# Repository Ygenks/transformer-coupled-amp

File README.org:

* Размер трансформатора ДхШ: 52.5х40

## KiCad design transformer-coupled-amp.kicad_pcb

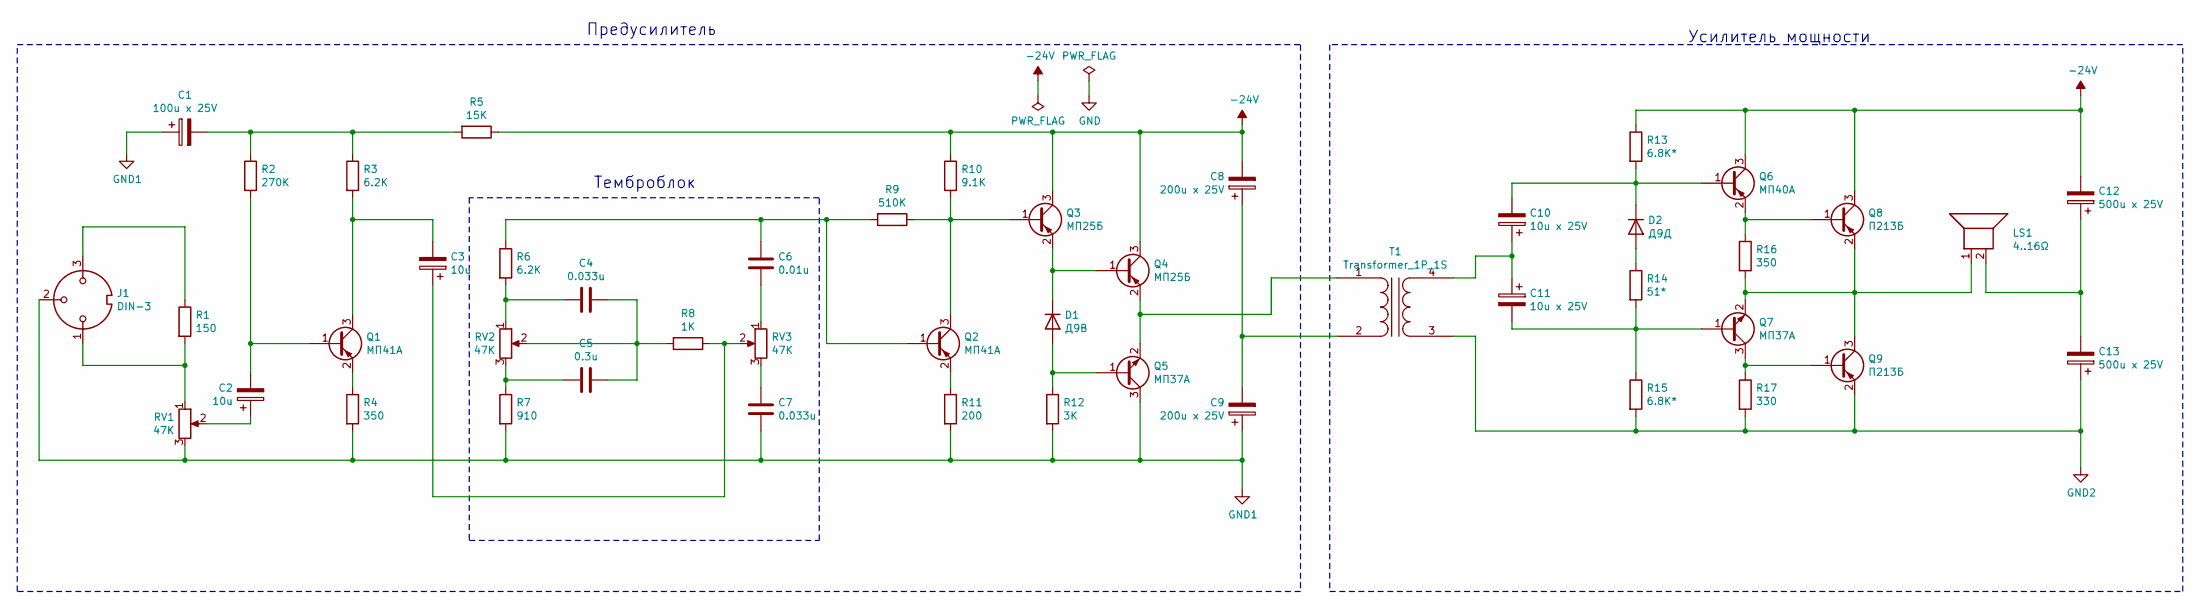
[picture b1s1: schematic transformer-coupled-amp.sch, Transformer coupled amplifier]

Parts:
C1: 100u x 25V; CP_Radial_D6.3mm_P2.50mm
C2, C3: 10u; CP_Radial_D5.0mm_P2.00mm
C4, C7: 0.033u; C_Disc_D10.0mm_W2.5mm_P5.00mm
C5: 0.3u; C_Rect_L18.0mm_W8.0mm_P15.00mm_FKS3_FKP3
C6: 0.01u; C_Rect_L13.0mm_W5.0mm_P10.00mm_FKS3_FKP3_MKS4
C8, C9: 200u x 25V; CP_Radial_D8.0mm_P3.50mm
C10, C11: 10u x 25V; CP_Radial_D5.0mm_P2.00mm
C12, C13: 500u x 25V; CP_Radial_D10.0mm_P5.00mm
D1: Д9В; D_DO-15_P15.24mm_Horizontal
D2: Д9Д; D_DO-15_P15.24mm_Horizontal
J1: DIN-3; PinHeader_1x03_P2.54mm_Vertical
LS1: 4..16Ω; PinHeader_1x02_P2.54mm_Vertical
Q1, Q2: МП41А; TO-5-3
Q3, Q4: МП25Б; TO-5-3
Q5, Q7: МП37А; TO-5-3
Q6: МП40A; TO-5-3
Q8, Q9: П213Б; PinHeader_1x03_P2.54mm_Vertical
R1: 150; R_Axial_DIN0207_L6.3mm_D2.5mm_P10.16mm_Horizontal
R2: 270K; R_Axial_DIN0207_L6.3mm_D2.5mm_P10.16mm_Horizontal
R3, R6: 6.2K; R_Axial_DIN0207_L6.3mm_D2.5mm_P10.16mm_Horizontal
R4: 350; R_Axial_DIN0207_L6.3mm_D2.5mm_P10.16mm_Horizontal
R5: 15K; R_Axial_DIN0207_L6.3mm_D2.5mm_P10.16mm_Horizontal
R7: 910; R_Axial_DIN0207_L6.3mm_D2.5mm_P10.16mm_Horizontal
R8: 1K; R_Axial_DIN0207_L6.3mm_D2.5mm_P10.16mm_Horizontal
R9: 510K; R_Axial_DIN0207_L6.3mm_D2.5mm_P10.16mm_Horizontal
R10: 9.1K; R_Axial_DIN0207_L6.3mm_D2.5mm_P10.16mm_Horizontal
R11: 200; R_Axial_DIN0207_L6.3mm_D2.5mm_P10.16mm_Horizontal
R12: 3K; R_Axial_DIN0207_L6.3mm_D2.5mm_P10.16mm_Horizontal
R13, R15: 6.8K*; R_Axial_DIN0309_L9.0mm_D3.2mm_P15.24mm_Horizontal
R14: 51*; R_Axial_DIN0309_L9.0mm_D3.2mm_P15.24mm_Horizontal
R16: 350; R_Axial_DIN0309_L9.0mm_D3.2mm_P15.24mm_Horizontal
R17: 330; R_Axial_DIN0309_L9.0mm_D3.2mm_P15.24mm_Horizontal
RV1, RV2, RV3: 47K; Potentiometer_Bourns_3386C_Horizontal
T1: Transformer_1P_1S; Transformer_44x40

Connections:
-24V: C8.2, C12.2, Q3.3 (C), Q4.3 (C), Q6.3 (C), Q8.3 (C), R5.1, R10.1, R13.1
GND1: C1.1, C7.2, C9.1, J1.2, Q5.3 (C), R4.2, R7.2, R11.2, R12.2, RV1.3
GND2: C13.1, Q9.2 (E), R15.2, R17.2, T1.3 (SA)
unnamed: C1.2, R2.1, R3.1, R5.2
unnamed: C2.1, RV1.2
unnamed: C2.2, Q1.1 (B), R2.2
unnamed: C3.1, R8.1, RV3.2
unnamed: C3.2, Q1.3 (C), R3.2
unnamed: C4.1, C5.1, R8.2, RV2.2
unnamed: C4.2, R6.2, RV2.1
unnamed: C5.2, R7.1, RV2.3
unnamed: C6.1, Q2.1 (B), R6.1, R9.2
unnamed: C6.2, RV3.1
unnamed: C7.1, RV3.3
unnamed: C8.1, C9.2, T1.2 (AB)
unnamed: C10.1, C11.1, T1.4 (SB)
unnamed: C10.2, D2.1 (K), Q6.1 (B), R13.2
unnamed: C11.2, Q7.1 (B), R14.2, R15.1
unnamed: C12.1, C13.2, LS1.2
unnamed: D1.1 (K), Q3.2 (E), Q4.1 (B)
unnamed: D1.2 (A), Q5.1 (B), R12.1
unnamed: D2.2 (A), R14.1
unnamed: J1.1, R1.2, RV1.1
unnamed: J1.3, R1.1
unnamed: LS1.1, Q7.2 (E), Q8.2 (E), Q9.3 (C), R16.2
unnamed: Q1.2 (E), R4.1
unnamed: Q2.2 (E), R11.1
unnamed: Q2.3 (C), Q3.1 (B), R9.1, R10.2
unnamed: Q4.2 (E), Q5.2 (E), T1.1 (AA)
unnamed: Q6.2 (E), Q8.1 (B), R16.1
unnamed: Q7.3 (C), Q9.1 (B), R17.1

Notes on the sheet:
Темброблок
Предусилитель
Усилитель мощности

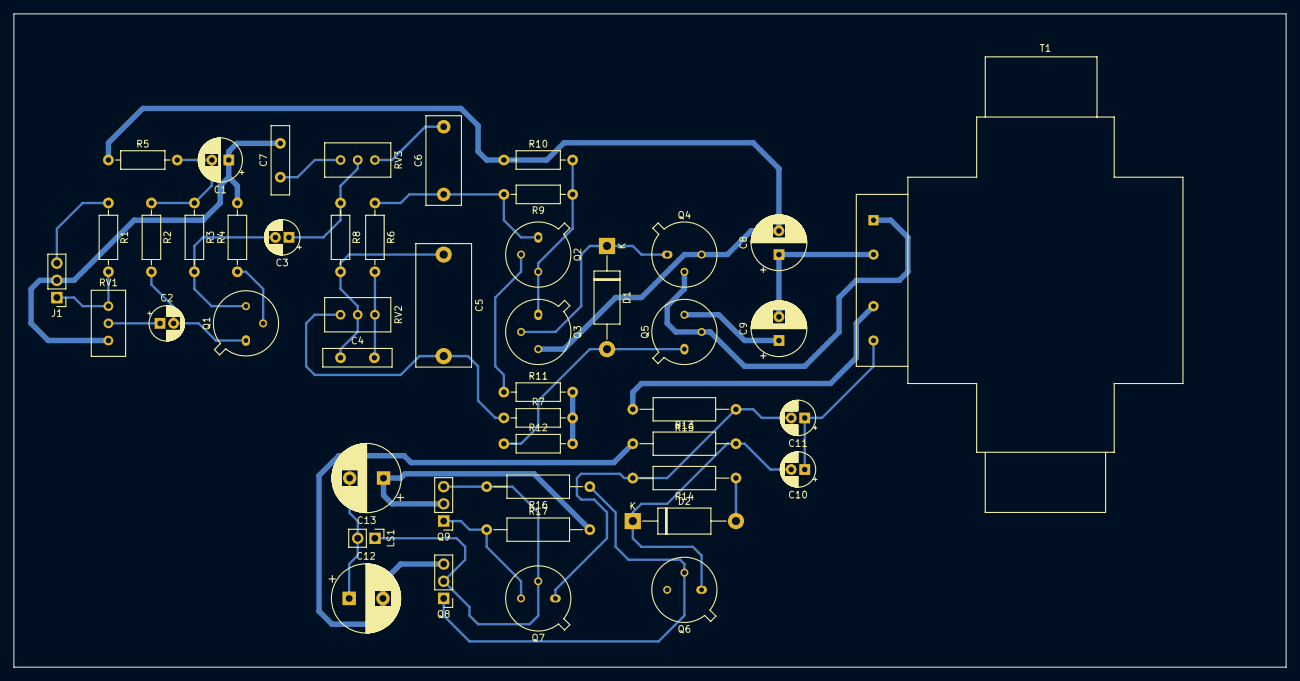
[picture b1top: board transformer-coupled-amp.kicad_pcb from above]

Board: 2 copper layers, 188.0 x 96.5 mm, 47 parts (0 on the bottom side), 31 nets.

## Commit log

2021-04-26 Strart drawing preamp part
2021-04-27 Annotate schematics
2021-04-27 Finish drawing schematics
2021-04-29 Add transformer size
2021-04-30 Assign footprints
2021-04-30 Start tracing pcb
2021-05-02 Add transformer footrpint
2021-05-17 Finish toneblock placement
2021-05-19 Route preamp
2021-05-20 Finish pcb routing
